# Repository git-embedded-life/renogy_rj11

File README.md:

# Intro
I have a Renogy Pure Sine Wave Inverter/Charger that I use to power my sump pump and server during a power outage. Recently I moved the inverter/charger from the basement to the garage which made my previous project of reading the display obsolete because I didn't want to suspend a Pi in front of the display only to have it bumped when somebody walked by. I still needed a way for the inverter to notify the attached computer when it was on battery, and when the battery was "low" so it could shut down cleanly.

The Renogy has a RJ11 port on it to connect a wired remote to. The remote has two LEDs on it: a green one that is solid when there is wall power, flashing when it is on battery, and a red one for error states. I figured I could reverse engineer this connection and use this port for the information I need. 

While with this I only will get On Wall/On Battery, I can make it work. The priority is the sump pump, so when power is lost I only want the computer to be up for a short period of time so most of the power is reserved for the sump pump. I just use a timer that is started when power is lost before reporting low battery.

# Setup

I use a NUT dummy UPS that from within the Python script it runs a NUT binary that updates the values of the dummy UPS. NUT 2.8 or higher is required for this and is not included in teh apt repo so I pulled it down from source.

## NUT Installation

```
# https://networkupstools.org/docs/user-manual.chunked/ar01s05.html

git clone https://github.com/networkupstools/nut.git
sudo useradd -r nut
sudo apt install autoconf automake libtool libssl-dev
./autogen.sh
./configure --with-user=nut --with-group=nut --without-nut-scanner --with-ssl --without-serial
make
sudo make install
mkdir -p /var/state/ups
sudo chmod 0770 /var/state/ups
sudo chown root:nut /var/state/ups
cp /usr/local/ups/etc/ups.conf.sample /usr/local/ups/etc/ups.conf
cp /usr/local/ups/etc/upsd.conf.sample /usr/local/ups/etc/upsd.conf
cp /usr/local/ups/etc/upsd.users.sample /usr/local/ups/etc/upsd.users
sudo chmod 640 /usr/local/ups/etc/upsd.users /usr/local/ups/etc/upsd.conf

# added 0.0.0.0 to /usr/local/ups/etc/upsd.conf

# enabled all nut unit files in /lib/systemd/system
```

/usr/local/ups/etc/ups.conf
```
[renogy]
        driver = dummy-ups
        port = renogy.dev
        # dummy-once is avaiable in 2.8.0 and prevents upsd from
        # overwritting values manipulated by upsrw
        mode = dummy-once
        desc = "Renogy UPS"
```

/usr/local/ups/etc/renogy.dev
```
device.mfr: Renogy
device.model: R-INVT-PCL1-30111S-US
device.type: ups
ups.mfr: Renogy
ups.model: R-INVT-PCL1-30111S-US
ups.status: OL
battery.runtime: 0
```

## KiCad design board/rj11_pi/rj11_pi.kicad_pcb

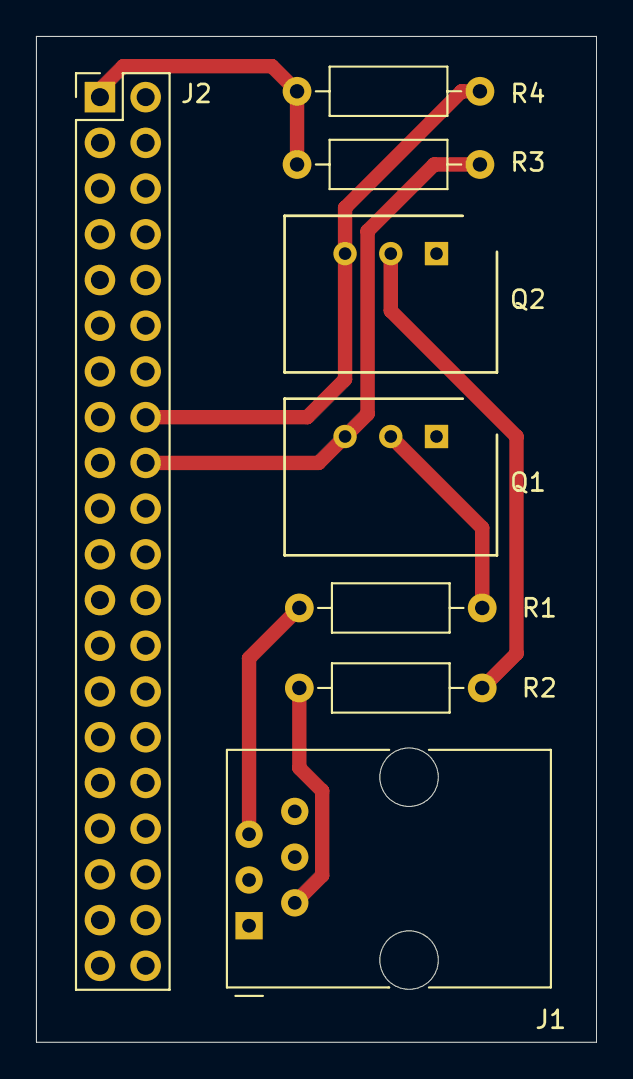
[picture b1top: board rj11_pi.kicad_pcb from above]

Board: 2 copper layers, 31.1 x 55.9 mm, 8 parts (0 on the bottom side), 8 nets.

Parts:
J1: 6P6C; RJ12_Amphenol_54601
J2: Conn_02x20_Odd_Even; PinHeader_2x20_P2.54mm_Vertical
Q1, Q2: Q_NPN_EBC; SIP3_11.6x8.5mm
R1, R2, R3, R4: R; R_Axial_DIN0207_L6.3mm_D2.5mm_P10.16mm_Horizontal

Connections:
+3V3: J2.1, R3.1, R4.1
GND: J1.1, J1.6, J2.6, J2.9, J2.14, J2.20, J2.25, J2.30, J2.34, J2.39, Q1.1, Q2.1
unnamed: J1.2, R2.2
unnamed: J1.5, R1.2
unnamed: J2.16, Q2.3, R4.2
unnamed: J2.18, Q1.3, R3.2
unnamed: Q1.2, R1.1
unnamed: Q2.2, R2.1

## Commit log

2022-09-20 initial release
2022-10-25 changed logging to print only when changed updated pins to work with pcb
